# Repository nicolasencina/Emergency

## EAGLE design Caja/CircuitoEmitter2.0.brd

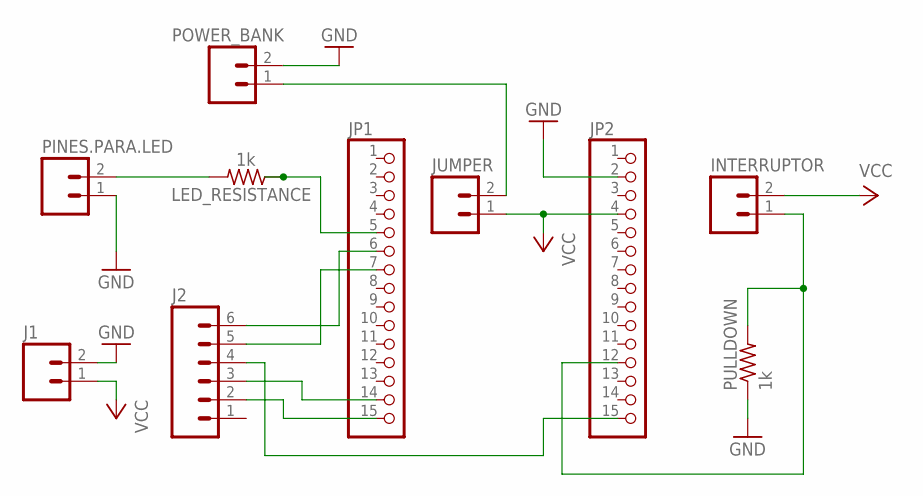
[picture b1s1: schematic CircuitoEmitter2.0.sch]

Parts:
INTERRUPTOR: M02LOCK_LONGPADS; 1X02_LOCK_LONGPADS
J1: M02LOCK_LONGPADS; 1X02_LOCK_LONGPADS
J2: M06LONGPADS; 1X06_LONGPADS
JP1, JP2: PINHD-1X15; 1X15
JUMPER: M02LOCK_LONGPADS; 1X02_LOCK_LONGPADS
LED_RESISTANCE: 1k; 0204/7
PINES.PARA.LED: M02LOCK_LONGPADS; 1X02_LOCK_LONGPADS
POWER_BANK: M02LOCK_LONGPADS; 1X02_LOCK_LONGPADS
PULLDOWN: 1k; 0204/7

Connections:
GND: J1.2, JP2.2, PINES.PARA.LED.1, POWER_BANK.2, PULLDOWN.1
unnamed: J2.5, JP1.7
unnamed: J2.4, JP2.15
unnamed: J2.3, JP1.14
unnamed: J2.2, JP1.15
unnamed: INTERRUPTOR.1, JP2.12, PULLDOWN.2
unnamed: JUMPER.2, POWER_BANK.1
unnamed: LED_RESISTANCE.2, PINES.PARA.LED.2
unnamed: JP1.5, LED_RESISTANCE.1
unnamed: J2.6, JP1.6
VCC: INTERRUPTOR.2, J1.1, JP2.4, JUMPER.1

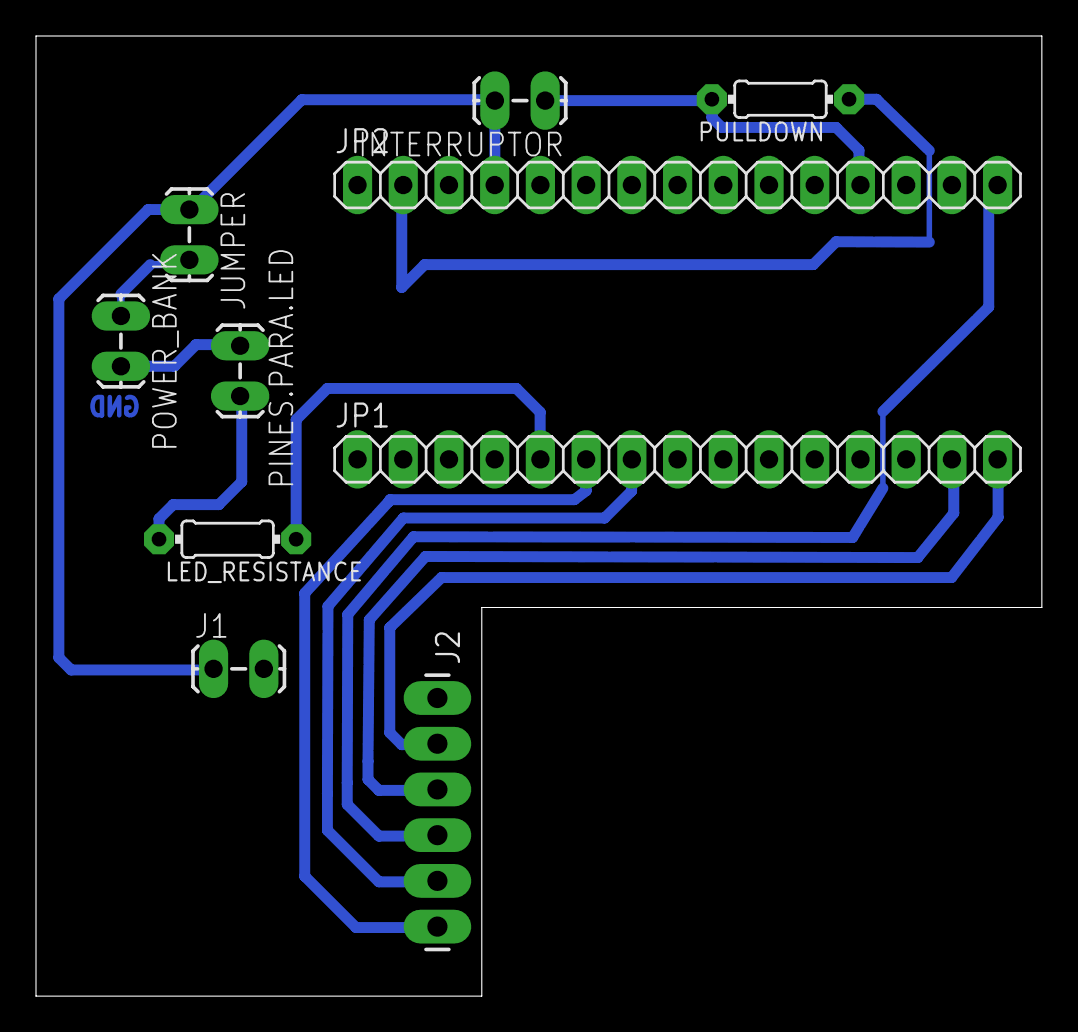
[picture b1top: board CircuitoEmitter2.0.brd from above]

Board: 2 copper layers, 55.9 x 53.3 mm, 10 parts (0 on the bottom side), 11 nets.

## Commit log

2016-06-15 Add basic code
2016-06-17 Actualizacion codigos
2016-09-13 Codigos casi listos 13/09
2016-09-13 Transmitter mejorado 13/09
2016-11-11 Codigo aún no funcional
2016-11-11 Implementacion Receiver con SerialDXL
2016-11-11 Fix merge
2016-11-11 Changed names
2016-11-12 Modelo Final PCB Boton node
2016-11-16 Rename Receiver_DXL.ino to receiver_dxl.ino
2016-11-16 Modificacion codigos transsmiter y receiver
2016-11-23 Agregada modalidad para ver calidad del servicio
